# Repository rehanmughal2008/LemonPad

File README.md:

# LemonPad
Building a macropad that I can use to quickly open my favorite apps like Discord, Apple Music, and Youtube.

Bill of Materials:
 -  1 unsoldered  [Seeed XIAO RP2040]([https://wiki.seeedstudio.com/XIAO-RP2040/](https://www.seeedstudio.com/XIAO-RP2040-v1-0-p-5026.html)) $3.99
 - 4x [MX-Style switches](https://www.aliexpress.us/item/3256804099108371.html?spm=a2g0o.productlist.main.8.68af2f7eWtFtOC&algo_pvid=a1e2d60d-07f5-4697-a957-d66a3413b436&algo_exp_id=a1e2d60d-07f5-4697-a957-d66a3413b436-7&pdp_ext_f=%7B%22order%22%3A%2213340%22%2C%22eval%22%3A%221%22%2C%22fromPage%22%3A%22search%22%7D&pdp_npi=6%40dis%21USD%214.18%210.99%21%21%214.18%210.99%21%402101e81117818405930291521e72db%2112000028628937410%21sea%21US%216354769134%21ABX%211%210%21n_tag%3A-29910%3Bd%3Ae72b2067%3Bm03_new_user%3A-29895%3BpisId%3A5000000207271026&curPageLogUid=aBMUsXnlj2BW&utparam-url=scene%3Asearch%7Cquery_from%3A%7Cx_object_id%3A1005004285423123%7C_p_origin_prod%3A) $3.96
 - 1x [EC11 Rotary encoders](https://www.aliexpress.us/item/3256810450545893.html?spm=a2g0o.productlist.main.1.30ce74654uhHeU&algo_pvid=8ffb863b-598b-45d3-a1fd-1b4b4fd8e1f1&algo_exp_id=8ffb863b-598b-45d3-a1fd-1b4b4fd8e1f1-4&pdp_ext_f=%7B%22order%22%3A%223503%22%2C%22eval%22%3A%221%22%2C%22fromPage%22%3A%22search%22%7D&pdp_npi=6%40dis%21USD%216.43%210.99%21%21%2143.42%216.73%21%402101dedf17818404295992043ef8a6%2112000053067832914%21sea%21US%216354769134%21ABX%211%210%21n_tag%3A-29910%3Bd%3Ae72b2067%3Bm03_new_user%3A-29895%3BpisId%3A5000000207262966&curPageLogUid=zsICwjLgUv2C&utparam-url=scene%3Asearch%7Cquery_from%3A%7Cx_object_id%3A1005010636860645%7C_p_origin_prod%3A) $6.43
 - 1x [0.91 inch OLED display](https://www.aliexpress.us/item/2251832702272500.html?spm=a2g0o.productlist.main.4.54edgtLKgtLK3n&algo_pvid=43430158-fd83-4626-8cdb-8555adf9011a&algo_exp_id=43430158-fd83-4626-8cdb-8555adf9011a-1&pdp_ext_f=%7B%22order%22%3A%22258%22%2C%22eval%22%3A%221%22%2C%22fromPage%22%3A%22search%22%7D&pdp_npi=6%40dis%21USD%211.23%210.99%21%21%211.23%210.99%21%402101d9ef17818402071164169eb4e0%2166455981607%21sea%21US%216354769134%21ABX%211%210%21n_tag%3A-29910%3Bd%3Ae72b2067%3Bm03_new_user%3A-29895%3BpisId%3A5000000208023469&curPageLogUid=L57EGcbASzRW&utparam-url=scene%3Asearch%7Cquery_from%3A%7Cx_object_id%3A32888587252%7C_p_origin_prod%3A) $1.23
 - 4x [white blank DSA keycaps](https://www.aliexpress.us/item/3256808457115497.html?spm=a2g0o.productlist.main.1.4edapsiNpsiNo9&algo_pvid=85a8432d-df2c-4e69-aed0-99208631399b&algo_exp_id=85a8432d-df2c-4e69-aed0-99208631399b-1&pdp_ext_f=%7B%22order%22%3A%2275%22%2C%22eval%22%3A%221%22%2C%22fromPage%22%3A%22search%22%7D&pdp_npi=6%40dis%21USD%214.72%210.99%21%21%214.72%210.99%21%402101df0e17818400643544065e5210%2112000046072492967%21sea%21US%216354769134%21ABX%211%210%21n_tag%3A-29910%3Bd%3Ae72b2067%3Bm03_new_user%3A-29895%3BpisId%3A5000000207271012&curPageLogUid=yqv1i3n7k4im&utparam-url=scene%3Asearch%7Cquery_from%3A%7Cx_object_id%3A1005008643430249%7C_p_origin_prod%3A) $4.81
- [4x M3x5mx4mm heatset inserts & 4x M3x16mm screws](https://www.aliexpress.us/item/3256808208664980.html?spm=a2g0o.productlist.main.27.6a78ZDUUZDUU8V&algo_pvid=b593d66d-9d84-442f-ad78-5d1b617f38c2&algo_exp_id=b593d66d-9d84-442f-ad78-5d1b617f38c2-45&pdp_ext_f=%7B%22order%22%3A%22581%22%2C%22eval%22%3A%221%22%2C%22fromPage%22%3A%22search%22%7D&pdp_npi=6%40dis%21USD%217.56%210.99%21%21%2151.02%216.66%21%40210311cc17818397442673974ec56c%2112000044841124242%21sea%21US%216354769134%21ABX%211%210%21n_tag%3A-29910%3Bd%3Ae72b2067%3Bm03_new_user%3A-29895%3BpisId%3A5000000207271026&curPageLogUid=6n5zhH3KMeRw&utparam-url=scene%3Asearch%7Cquery_from%3A%7Cx_object_id%3A1005008394979732%7C_p_origin_prod%3A) $7.56
- 5x [Custom PCB from PCBWay] Rounded up estimate: $18
- 1x [Custom 3D prints from PCBWay] Rounded up estimate: $13

TOTAL = $53.57 ($35.33 + $18.24 Shipping)

IMAGES:

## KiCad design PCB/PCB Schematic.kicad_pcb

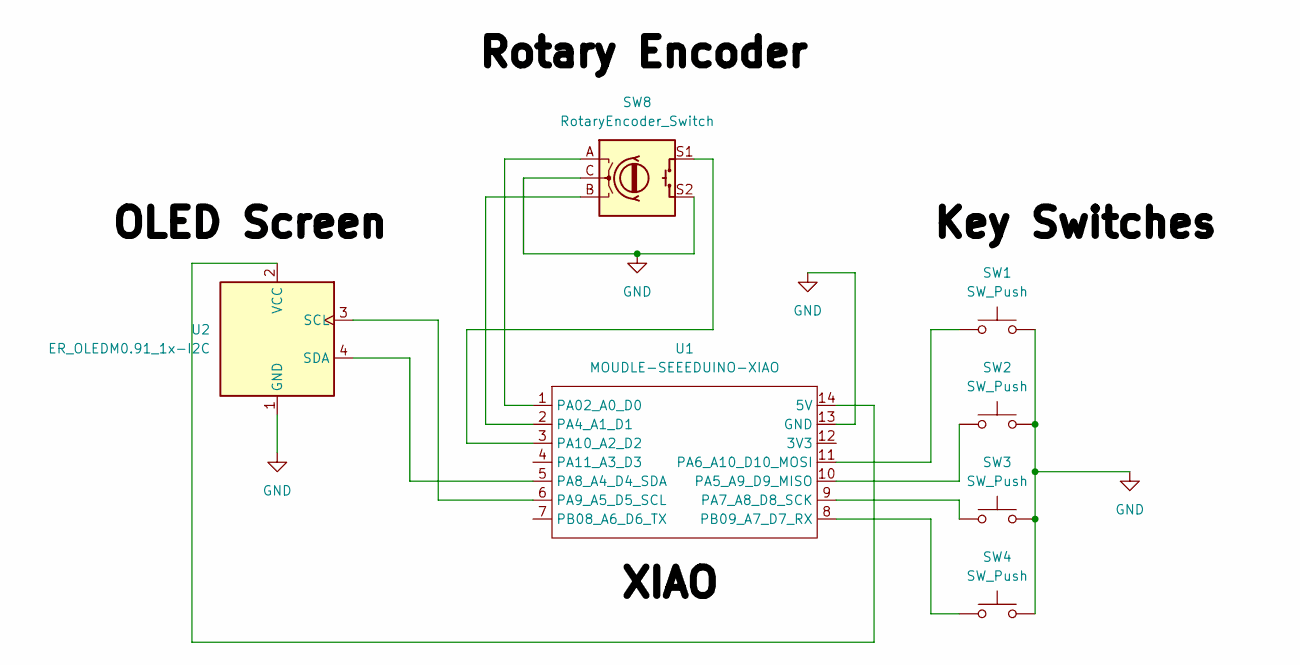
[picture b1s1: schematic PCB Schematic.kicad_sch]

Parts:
SW1, SW2, SW3, SW4: SW_Push; SW_Cherry_MX_1.00u_PCB
SW8: RotaryEncoder_Switch; RotaryEncoder_Alps_EC11E-Switch_Vertical_H20mm
U1: MOUDLE-SEEEDUINO-XIAO; XIAO-Generic-Hybrid-14P-2.54-21X17.8MM
U2: ER_OLEDM0.91_1x-I2C

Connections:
GND: SW1.1, SW2.1, SW3.1, SW4.1, SW8.C, SW8.S2, U1.13 (GND), U2.1 (GND)
unnamed: U1.14 (5V), U2.2 (VCC)
unnamed: SW8.A, U1.1 (PA02_A0_D0)
unnamed: SW8.B, U1.2 (PA4_A1_D1)
unnamed: SW2.2, U1.10 (PA5_A9_D9_MISO)
unnamed: SW1.2, U1.11 (PA6_A10_D10_MOSI)
unnamed: SW3.2, U1.9 (PA7_A8_D8_SCK)
unnamed: U1.5 (PA8_A4_D4_SDA), U2.4 (SDA)
unnamed: U1.6 (PA9_A5_D5_SCL), U2.3 (SCL)
unnamed: SW8.S1, U1.3 (PA10_A2_D2)
unnamed: SW4.2, U1.8 (PB09_A7_D7_RX)

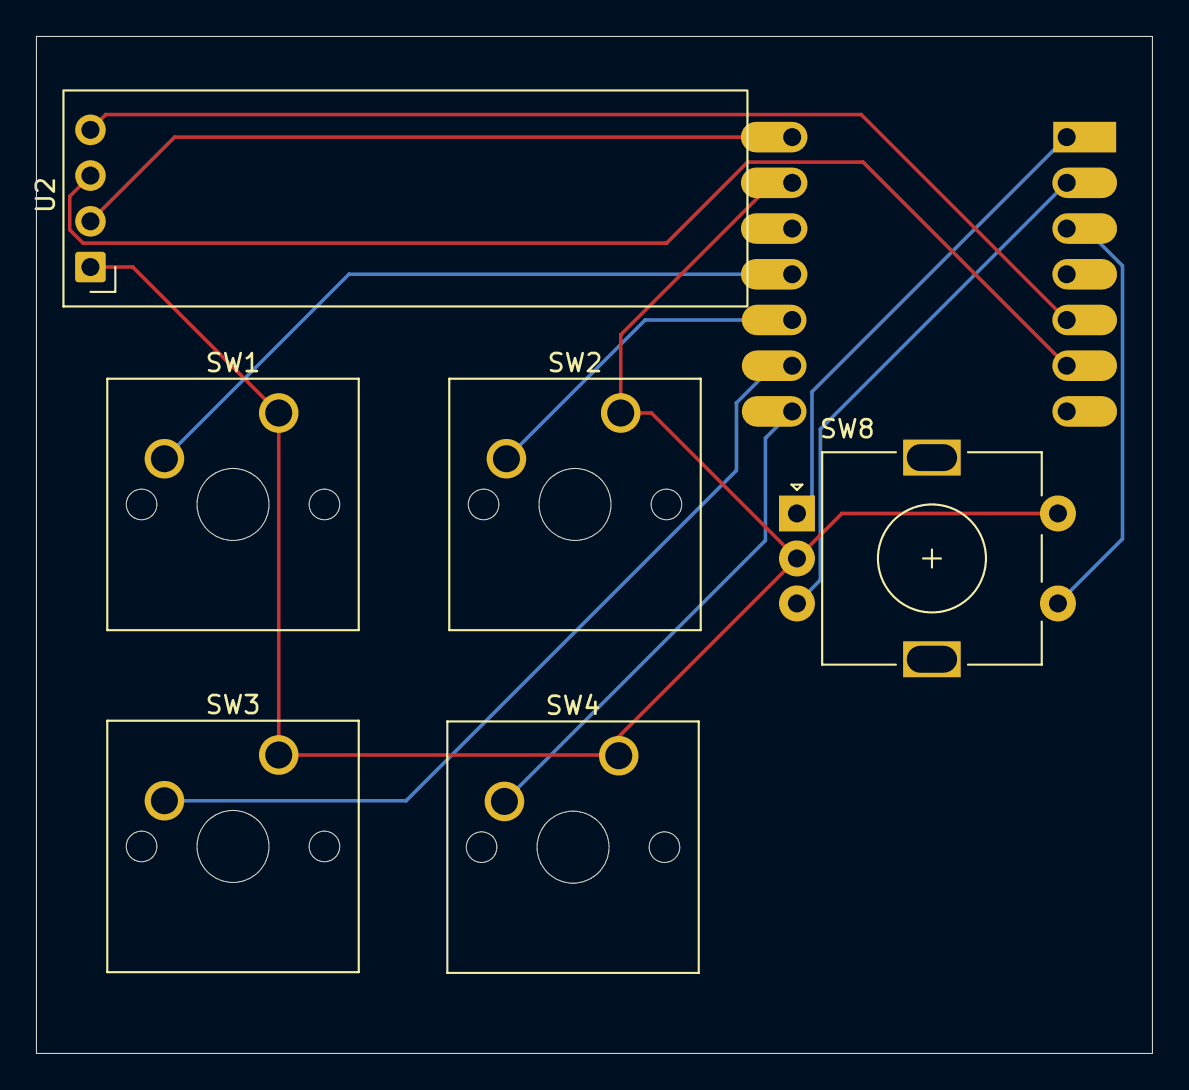
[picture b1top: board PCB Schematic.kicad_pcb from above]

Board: 2 copper layers, 62.0 x 56.5 mm, 7 parts (1 on the bottom side), 11 nets.

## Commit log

2026-06-14 Adding Files to Repo
2026-06-14 Adding main.py Firmware
2026-06-14 Adding Images
2026-06-14 Update README with project details and materials
    Added a project description and bill of materials to README.
2026-06-16 Changed images and model designs
2026-06-16 Adding images to README
2026-06-19 Updated sourcing and prices
